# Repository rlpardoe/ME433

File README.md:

Robert Pardoe's Repo for Northwestern Universities MECH_ENG 433 Class

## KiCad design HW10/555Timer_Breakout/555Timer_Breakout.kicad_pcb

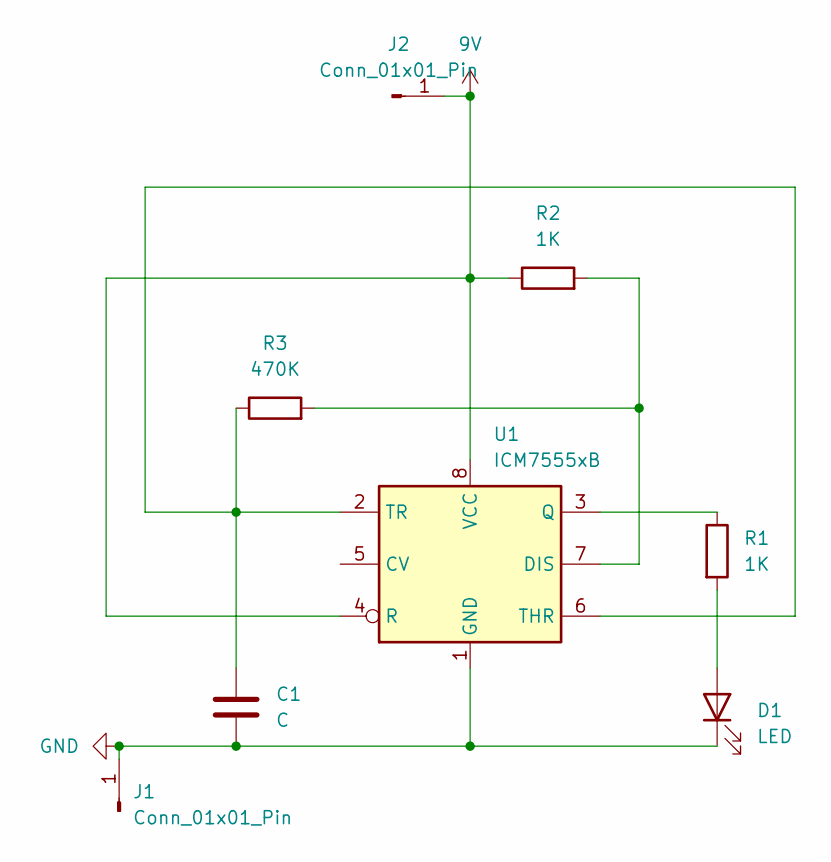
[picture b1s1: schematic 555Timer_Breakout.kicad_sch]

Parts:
C1: C; CP_Elec_4x5.3
D1: LED; LED_2512_6332Metric_Pad1.52x3.35mm_HandSolder
J1, J2: Conn_01x01_Pin
R1, R2: 1K; R_0805_2012Metric_Pad1.20x1.40mm_HandSolder
R3: 470K; R_0805_2012Metric_Pad1.20x1.40mm_HandSolder
U1: ICM7555xB; SOIC-8_3.9x4.9mm_P1.27mm

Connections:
9V: J2.1, R2.1, U1.4 (R), U1.8 (VCC)
GND: C1.2, D1.1 (K), J1.1, U1.1 (GND)
unnamed: D1.2 (A), R1.2
unnamed: R2.2, R3.2, U1.7 (DIS)
unnamed: R1.1, U1.3 (Q)
unnamed: C1.1, R3.1, U1.2 (TR), U1.6 (THR)

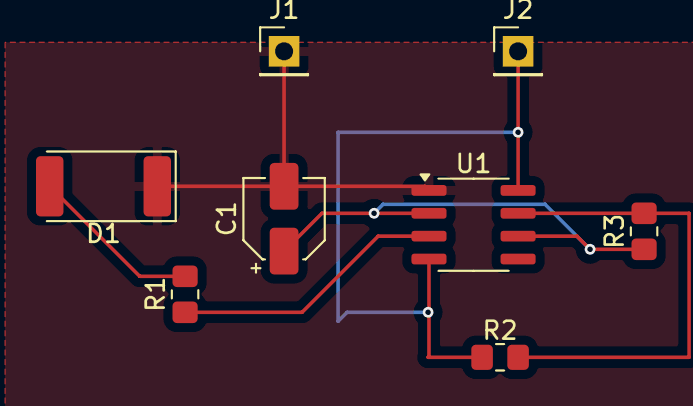
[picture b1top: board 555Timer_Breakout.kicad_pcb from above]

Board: 2 copper layers, 8 parts (0 on the bottom side), 6 nets.

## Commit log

2024-04-03 Wrote and Built Blink for 5 Hz
2024-04-04 HW3 Code
2024-04-11 HW4 and folder for HW5
2024-04-16 Finished Code
2024-04-18 HW6 Finished
2024-04-20 Started files
2024-05-12 Finished HW7
2024-05-24 HW9 complete
2024-05-24 Multi Digit Integers
2024-05-25 hw12 complete
2024-05-26 HW16
2024-05-27 both motors
2024-05-27 Made mount
2024-05-30 Started hw11 and hw13
2024-05-31 Semi-Working Robot Code!
2024-05-31 Robot Video
2024-06-04 PCB design
2024-06-04 PNGs added
2024-08-10 hw14 unfinished setup
